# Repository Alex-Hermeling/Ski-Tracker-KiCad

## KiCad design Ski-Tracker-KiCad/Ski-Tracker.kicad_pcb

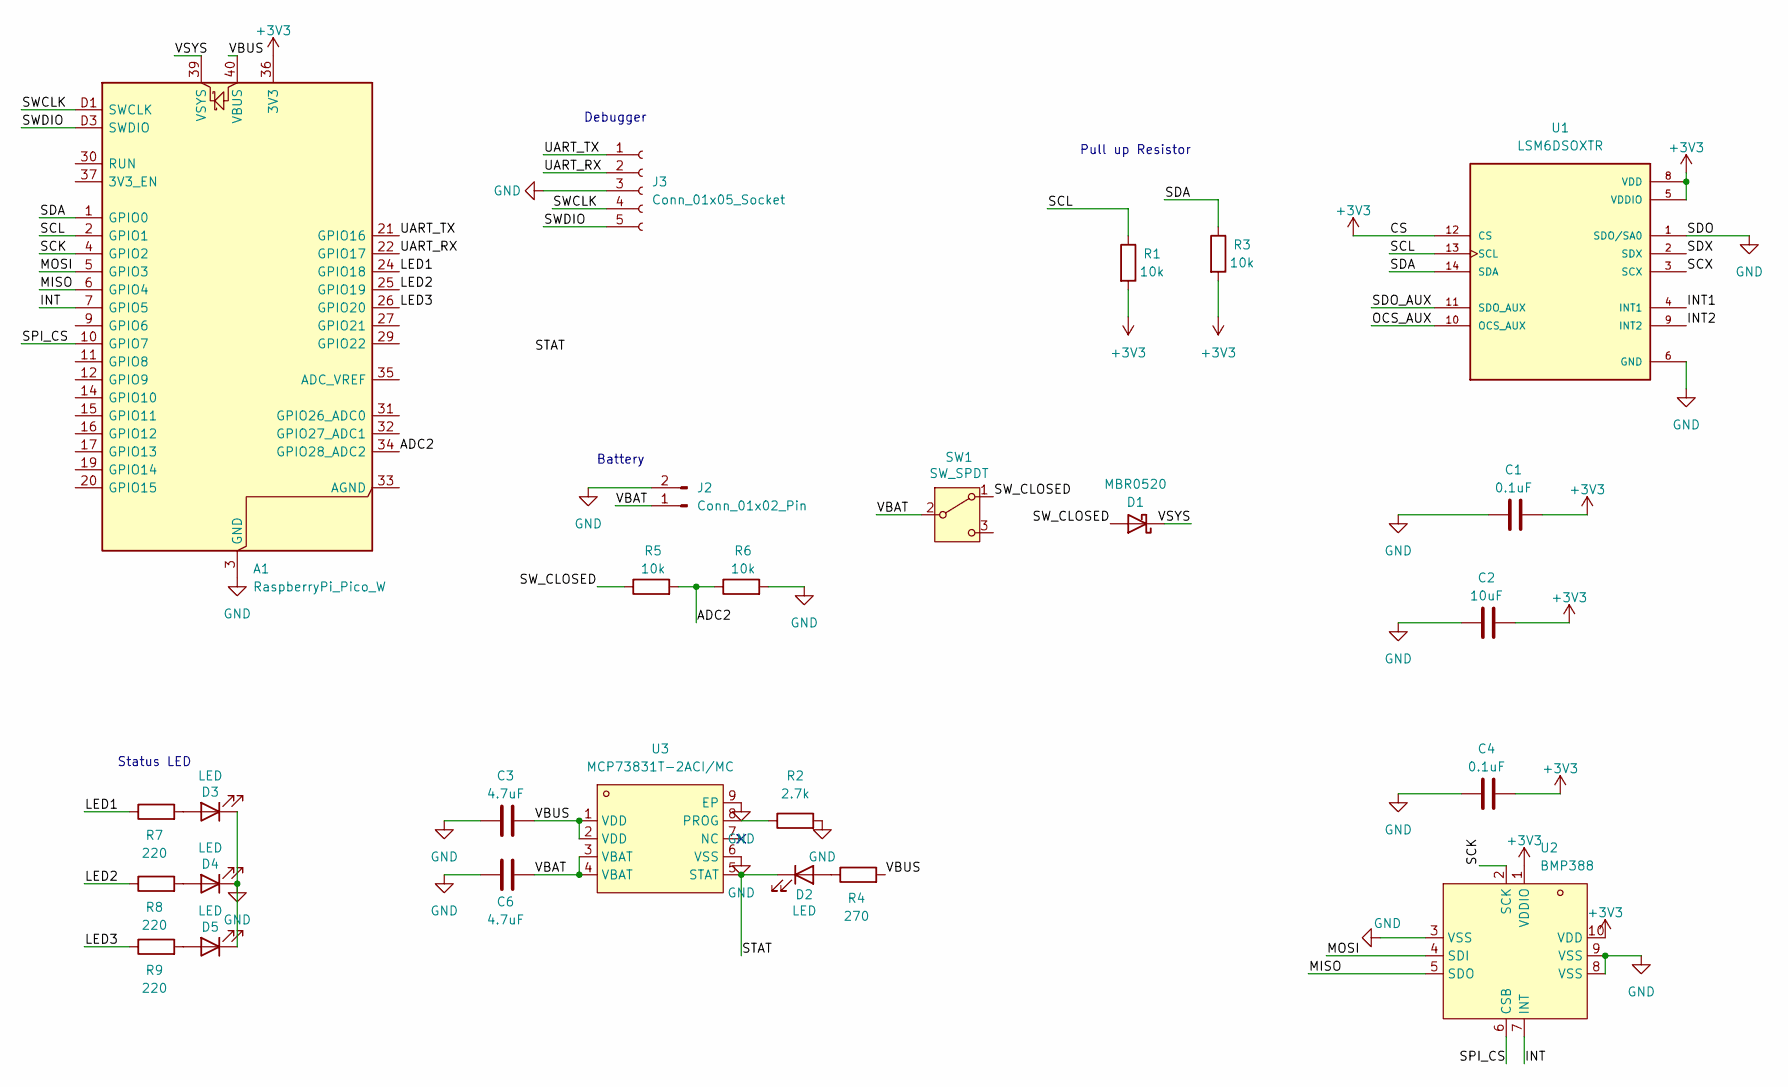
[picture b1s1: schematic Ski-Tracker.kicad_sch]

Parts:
A1: RaspberryPi_Pico_W; RaspberryPi_Pico_W_SMD_HandSolder
C1, C4: 0.1uF; C_0402_1005Metric
C2: 10uF; C_0805_2012Metric
C3, C6: 4.7uF; C_0805_2012Metric
D1: MBR0520; SOD-123_L2.8-W1.8-LS3.7-RD
D2: LED; LED_0603_1608Metric
D3, D4, D5: LED; LED_0805_2012Metric
J2: Conn_01x02_Pin; JST_PH_S2B-PH-K_1x02_P2.00mm_Horizontal
J3: Conn_01x05_Socket; JST_PH_S5B-PH-K_1x05_P2.00mm_Horizontal
R1, R3, R5, R6: 10k; R_0402_1005Metric
R2: 2.7k; R_0603_1608Metric
R4: 270; R_0603_1608Metric
R7, R8, R9: 220; R_0603_1608Metric
SW1: SW_SPDT; HorizontalSW
U1: LSM6DSOXTR; PQFN50P250X300X86-14N; PARTREV 3.0
U2: BMP388; SENSORM-SMD_BMP388; LCSC Part C779278
U3: MCP73831T-2ACI/MC; DFN-8_L3.0-W2.0-P0.50-BL-EP1.6; LCSC Part C411870

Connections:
+3V3: A1.36 (3V3), C1.2, C2.2, C4.2, R1.2, R3.2, U1.5 (VDDIO), U1.8 (VDD), U1.12 (CS), U2.1 (VDDIO), U2.10 (VDD)
/ADC2: A1.34 (GPIO28_ADC2), R5.2, R6.1
/INT: A1.7 (GPIO5), U2.7 (INT)
/INT1: U1.4 (INT1)
/INT2: U1.9 (INT2)
/LED1: A1.24 (GPIO18), R7.1
/LED2: A1.25 (GPIO19), R8.1
/LED3: A1.26 (GPIO20), R9.1
/MISO: A1.6 (GPIO4), U2.5 (SDO)
/MOSI: A1.5 (GPIO3), U2.4 (SDI)
/OCS_AUX: U1.10 (OCS_AUX)
/SCK: A1.4 (GPIO2), U2.2 (SCK)
/SCL: A1.2 (GPIO1), R1.1, U1.13 (SCL)
/SCX: U1.3 (SCX)
/SDA: A1.1 (GPIO0), R3.1, U1.14 (SDA)
/SDO_AUX: U1.11 (SDO_AUX)
/SDX: U1.2 (SDX)
/SPI_CS: A1.10 (GPIO7), U2.6 (CSB)
/STAT: D2.1 (K), U3.5 (STAT)
/SWCLK: A1.D1 (SWCLK), J3.4
/SWDIO: A1.D3 (SWDIO), J3.5
/SW_CLOSED: D1.2 (A), R5.1, SW1.1 (A)
/UART_RX: A1.22 (GPIO17), J3.2
/UART_TX: A1.21 (GPIO16), J3.1
/VBAT: C6.1, J2.1, SW1.2 (B), U3.3 (VBAT), U3.4 (VBAT)
/VBUS: A1.40 (VBUS), C3.2, R4.2, U3.1 (VDD), U3.2 (VDD)
/VSYS: A1.39 (VSYS), D1.1 (K)
GND: A1.3 (GND), A1.8 (GND), A1.13 (GND), A1.18 (GND), A1.23 (GND), A1.28 (GND), A1.38 (GND), A1.D2 (GND), C1.1, C2.1, C3.1, C4.1, C6.2, D3.1 (K), D4.1 (K), D5.1 (K), J2.2, J3.3, R2.2, R6.2, U1.1 (SDO/SA0), U1.6 (GND), U1.7 (GND), U2.3 (VSS), U2.8 (VSS), U2.9 (VSS), U3.6 (VSS), U3.9 (EP)
unnamed: D2.2 (A), R4.1
unnamed: D3.2 (A), R7.2
unnamed: D4.2 (A), R8.2
unnamed: D5.2 (A), R9.2
unnamed: R2.1, U3.8 (PROG)

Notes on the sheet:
Status LED
Debugger
Pull up Resistor
Battery

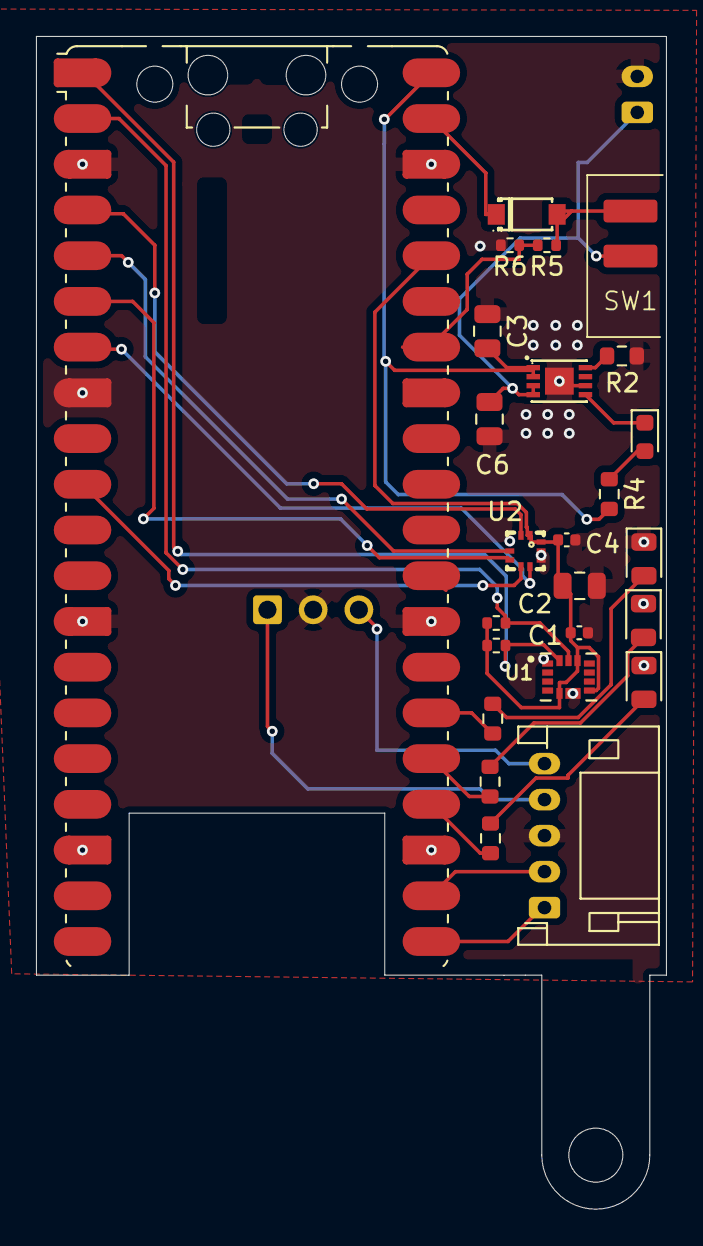
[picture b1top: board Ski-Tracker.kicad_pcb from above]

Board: 2 copper layers, 35.0 x 65.2 mm, 26 parts (1 on the bottom side), 27 nets.

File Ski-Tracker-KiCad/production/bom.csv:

Designator,Footprint,Quantity,Value,LCSC Part #
A1,RaspberryPi_Pico_W_SMD_HandSolder,1,RaspberryPi_Pico_W,
"C1, C4",0402,2,0.1uF,
C2,0805,1,10uF,
"C3, C6",0805,2,4.7uF,
D1,SOD-123_L2.8-W1.8-LS3.7-RD,1,1N5817,
D2,0603,1,LED,
"D3, D4, D5",0805,3,LED,
J2,JST_PH_S2B-PH-K_1x02_P2.00mm_Horizontal,1,Conn_01x02_Pin,
J3,JST_PH_S5B-PH-K_1x05_P2.00mm_Horizontal,1,Conn_01x05_Socket,
"R1, R3, R5, R6",0402,4,10k,
R2,0603,1,2.7k,
R4,0603,1,270,
"R7, R8, R9",0603,3,220,
SW1,HorizontalSW,1,SW_SPDT,
U1,PQFN50P250X300X86-14N,1,LSM6DSOXTR,
U2,SENSORM-SMD_BMP388,1,BMP388,C779278
U3,DFN-8_L3.0-W2.0-P0.50-BL-EP1.6,1,MCP73831T-2ACI/MC,C411870

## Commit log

2026-03-20 First time using copperPilot
2026-03-23 small changes
2026-03-24 changed diode value
2026-03-31 Status LED
2026-03-31 Add production directory
2026-04-20 KiCad 10 update
